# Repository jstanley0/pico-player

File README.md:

# pico-player
Music player for Raspberry Pi Pico and a pair of SN76489s

## Installation
 * Copy the contents of `firmware` (`sound.py` and `music_player.py` to your Pico), via `rshell cp firmware/* /pyboard` or pasting into Thonny, etc.
 
## Playing songs from the Pico's file system
 * On your computer, run `python3 util/convert_midi.py example.mid example.dat`
 * Copy the output to the Pico via e.g. `rshell cp example.dat /pyboard`. It is a binary file so pasting it via an IDE isn't going to work.
 * On the Pico, instantiate a MusicPlayer and play the song:
```
from music_player import MusicPlayer
mp = MusicPlayer()
mp.play_song('example.dat')
```
## Playing MIDI files from a connected computer
 * run `python3 util/convert_midi.py example.mid -` 

## How it works
 * A (very) short PIO program clocks both sound chips. This could also be done with PWM, but the fractional multiplier on the Pico's PIO controller gives us a lot of flexibility on what frequency to clock the chips at, and since the chip has only a 10-bit frequency register, there are tradeoffs between clock rate and usable note range.
 * Another short PIO program sends data to both chips. It just tosses 10 bits at the first ten GPIOs, where the first eight go to both chips' data lines, and the last two go to each chip's Write Enable line. By setting exactly one of those bits, I control which sound chip latches the value. The PIO program then waits the requisite 32 cycles for the SN76489 to complete the I/O, while the main Python program keeps running! It just tosses a value in the FIFO and forgets. It's magic.
 * A timer callback fires every 50ms and manages the sound envelope for each playing note, and also updates the brightness of each LED.
 * The LEDs are managed with PWM. The Pico has *sixteen* PWM channels and they work with *any* of the GPIOs. It's magic.
 
## The hard part
Getting music data into a usable format is tricky. I wrote a script (util/convert_midi.py) that translates note-on and note-off events into a simple binary format that the microcontroller program can parse and play. The primary challenge is that we have only six notes of polyphony to work with, so it works best with simple MIDI files. I suggest opening files in e.g. MuseScore beforehand to identify channels to prioritize (with -p) or exclude (with -x). If no arguments are given, convert_midi.py will prioritize channels in tracks named "melody" or "vocals".
 
## Bill of Materials
 * one Raspberry Pi Pico
 * two SN76489 sound chips
 * two 10uF electrolytic capacitors (the value isn't critical)
 * one stereo 3.5mm audio jack (CUI SJ1-3533NG)
 * (optionally) one dual-gang 10k potentiometer for volume control (Alps RK09L)
 
## Wiring (see KiCad schematic in hardware/pico-player-pcb)

 * VBUS to both chips' VCC (pin 16)
 * GND to both chips' GND (pin 8)
 * GPIOs 0..7 to the data lines of both sound chips in parallel (GPIO 0 to pin 10)
 * GPIO 8 to the left chip's /WE line (pin 5)
 * GPIO 9 to the right chip's /WE line
 * GPIO 10 to the left chip's /OE line (pin 6)
 * GPIO 11 to the right chip's /OE line
 * GPIO 12 to both chips' clock (pin 14)
 * Both sound chips' READY disconnected (it's 5V logic anyway)
 * GPIOs 15..22 to the blinkenlights!

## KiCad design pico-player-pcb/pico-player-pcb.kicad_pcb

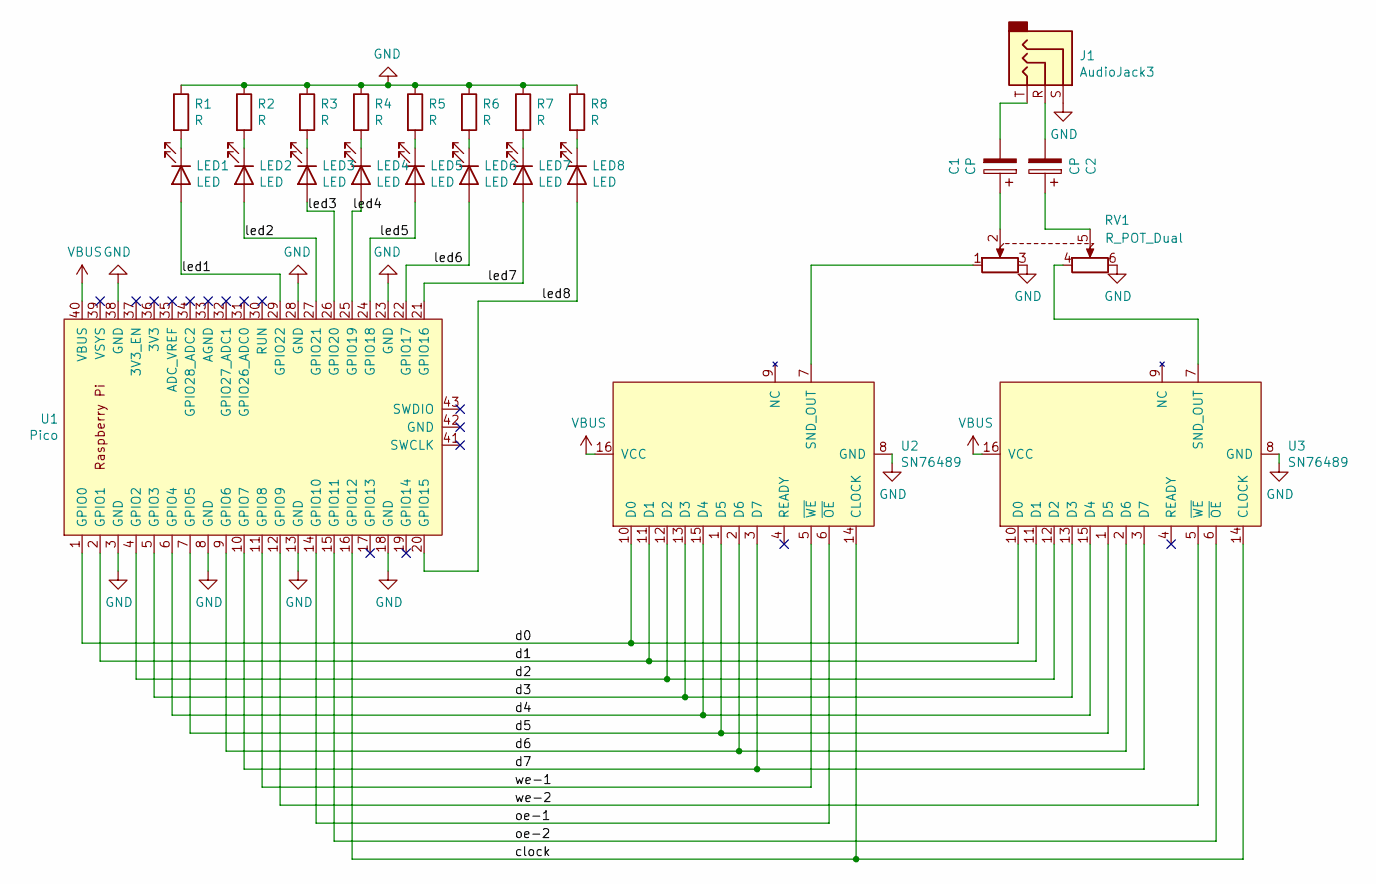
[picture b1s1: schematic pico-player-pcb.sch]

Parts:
C1, C2: CP; CP_Radial_D5.0mm_P2.50mm
J1: AudioJack3; Jack_3.5mm_CUI_SJ1-3533NG_Horizontal
LED1, LED2, LED3, LED4, LED5, LED6, LED7, LED8: LED; LED_D5.0mm_Clear
R1, R2, R3, R4, R5, R6, R7, R8: R; R_Axial_DIN0309_L9.0mm_D3.2mm_P2.54mm_Vertical
RV1: R_POT_Dual; Potentiometer_Alps_RK09L_Double_Vertical
U1: Pico; RPi_Pico_SMD_TH
U2, U3: SN76489; DIP-16_W7.62mm

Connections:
/clock: U1.16 (GPIO12), U2.14 (CLOCK), U3.14 (CLOCK)
/d0: U1.1 (GPIO0), U2.10 (D0), U3.10 (D0)
/d1: U1.2 (GPIO1), U2.11 (D1), U3.11 (D1)
/d2: U1.4 (GPIO2), U2.12 (D2), U3.12 (D2)
/d3: U1.5 (GPIO3), U2.13 (D3), U3.13 (D3)
/d4: U1.6 (GPIO4), U2.15 (D4), U3.15 (D4)
/d5: U1.7 (GPIO5), U2.1 (D5), U3.1 (D5)
/d6: U1.9 (GPIO6), U2.2 (D6), U3.2 (D6)
/d7: U1.10 (GPIO7), U2.3 (D7), U3.3 (D7)
/led1: LED1.2 (A), U1.29 (GPIO22)
/led2: LED2.2 (A), U1.27 (GPIO21)
/led3: LED3.2 (A), U1.26 (GPIO20)
/led4: LED4.2 (A), U1.25 (GPIO19)
/led5: LED5.2 (A), U1.24 (GPIO18)
/led6: LED6.2 (A), U1.22 (GPIO17)
/led7: LED7.2 (A), U1.21 (GPIO16)
/led8: LED8.2 (A), U1.20 (GPIO15)
/oe-1: U1.14 (GPIO10), U2.6 (~OE)
/oe-2: U1.15 (GPIO11), U3.6 (~OE)
/we-1: U1.11 (GPIO8), U2.5 (~WE)
/we-2: U1.12 (GPIO9), U3.5 (~WE)
GND: J1.S, R1.1, R2.1, R3.1, R4.1, R5.1, R6.1, R7.1, R8.1, RV1.3, RV1.6, U1.3 (GND), U1.8 (GND), U1.13 (GND), U1.18 (GND), U1.23 (GND), U1.28 (GND), U1.38 (GND), U2.8 (GND), U3.8 (GND)
unnamed: C1.1, RV1.2
unnamed: C1.2, J1.T
unnamed: C2.1, RV1.5
unnamed: C2.2, J1.R
unnamed: LED1.1 (K), R1.2
unnamed: LED2.1 (K), R2.2
unnamed: LED3.1 (K), R3.2
unnamed: LED4.1 (K), R4.2
unnamed: LED5.1 (K), R5.2
unnamed: LED6.1 (K), R6.2
unnamed: LED7.1 (K), R7.2
unnamed: LED8.1 (K), R8.2
unnamed: RV1.1, U2.7 (SND_OUT)
unnamed: RV1.4, U3.7 (SND_OUT)
VBUS: U1.40 (VBUS), U2.16 (VCC), U3.16 (VCC)

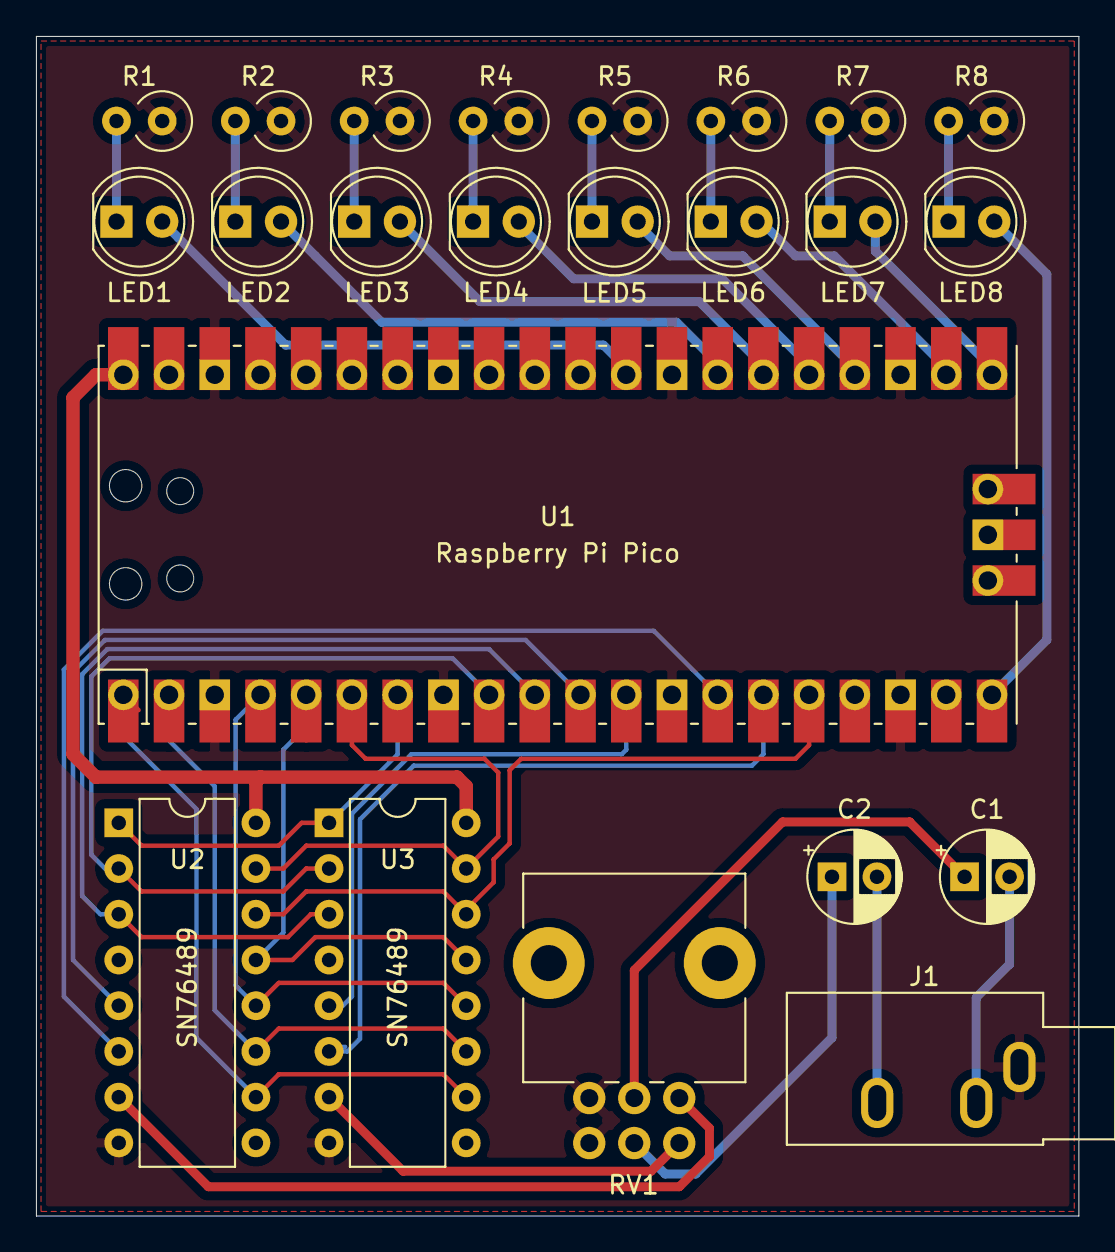
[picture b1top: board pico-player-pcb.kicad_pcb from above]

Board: 2 copper layers, 57.9 x 65.5 mm, 23 parts (0 on the bottom side), 37 nets.

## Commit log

2021-02-08 initial commit; very WIP
2021-02-09 checkpoint
    still very wip
2021-02-09 I'd say it compiles but it's interpreted
    e.g., it runs, and it produces output. I can't evaluate how
    good the output is until I write the thing that consumes it :P
2021-02-09 apparently I need D1 for my example file
    really, I need to make this frequency thing dynamic,
    based on the range of the song!
2021-02-10 some code generation optimizations
    * temporally consolidate note-off and note-on events
    when separated by less than 10ms
    * skip unnecessary note-off events when starting a
    new note immediately in the voice
    * use a single 16-bit message to turn off an arbitrary set
    of voices instead of one 8-bit message per voice
2021-02-10 kind of working implementation
    still need to do envelopes, and possibly make delays smarter
2021-02-10 envelope handling and cleanup
    protip: ALWAYS deinit your timer in a finally block
2021-02-10 fix deinit order
2021-02-10 fix note-off-by-one error
2021-02-10 tweak dynamics and lights
2021-02-11 a bad experiment
2021-02-11 Create LICENSE
2021-02-12 translate midi notes in player rather than converter
    this has a few advantages:
    * the song format is independent of the SN76489 frequency
    * we save three bits in the song format, making room for
    more dynamics bits
    the disadvantage is songs can't represent arbitrary frequencies
    but was I really going to use this project for my microtonal
2021-02-12 delay at end of song
    to let notes finish fading out
2021-02-13 don't require a total order for priority
    simply have priority channels and excluded channels
    also don't have preferred voices; use the least-recently used
    voice on the channel's preferred chip instead, to maximize
    release time
    and tweak velocity/attenuation mapping again
2021-02-13 I guess I can't check there after all
2021-02-16 schematic and PCB (untested)
2021-02-16 minor pcb tweak
2021-02-16 protip: draw your traces and then don't look at them again
2021-02-19 I think probably the pot was wired backward
2021-02-26 ... sigh, it was better before
2021-02-27 adjust to match the PCB
2021-03-12 rearrange slightly
    the potentiometer was upside-down, at least when you install
    a knob with a marker
    it's nice to have the audio jack on the side, so you can
    stand the board up
2021-03-13 add noise channel LEDs
    (they're not actually used yet)
2021-03-13 add video to readme
2021-03-21 automatically prioritize channels in "melody" or "vocals" track
2021-04-04 fewer underscores
    I am a Rubyist who only pretends to know Python
2021-04-04 normalize volumes
2021-04-05 add percussion, sort of
    still haven't implemented varying decay envelopes
2021-04-05 tweak percussion, implement varying decay envelopes
2021-04-05 attenuate closed hi-hat
    because otherwise it's indistinguishable from the snare
2021-04-05 tweaks
2021-04-06 hopefully "fix" the intermittent hanging problem
    occasionally utime.sleep_ms() failed to wake up. I suspect it
    involved some kind of a race condition involving the Timer
    because I never saw the problem occur with envelopes disabled
    but envelopes are required for percussion (and also the
    frequency of the callback has increased)
    this workaround seems okay so far
2021-04-08 upload schematic as image
    for mere mortals who want to build this thing on a breadboard and definitely do not want to involve KiCad
2021-04-08 add schematic to readme
2021-04-25 add ability to stream a midi file directly to the pico
    pass - as the output file parameter to util/convert_midi.py,
    and it will connect to the Pico over USB and play music by
    sending small chunks of data over the REPL. no need to copy
    files to the Pico's file system anymore. (other than the
    actual music player, of course)
2021-04-26 shortcut
